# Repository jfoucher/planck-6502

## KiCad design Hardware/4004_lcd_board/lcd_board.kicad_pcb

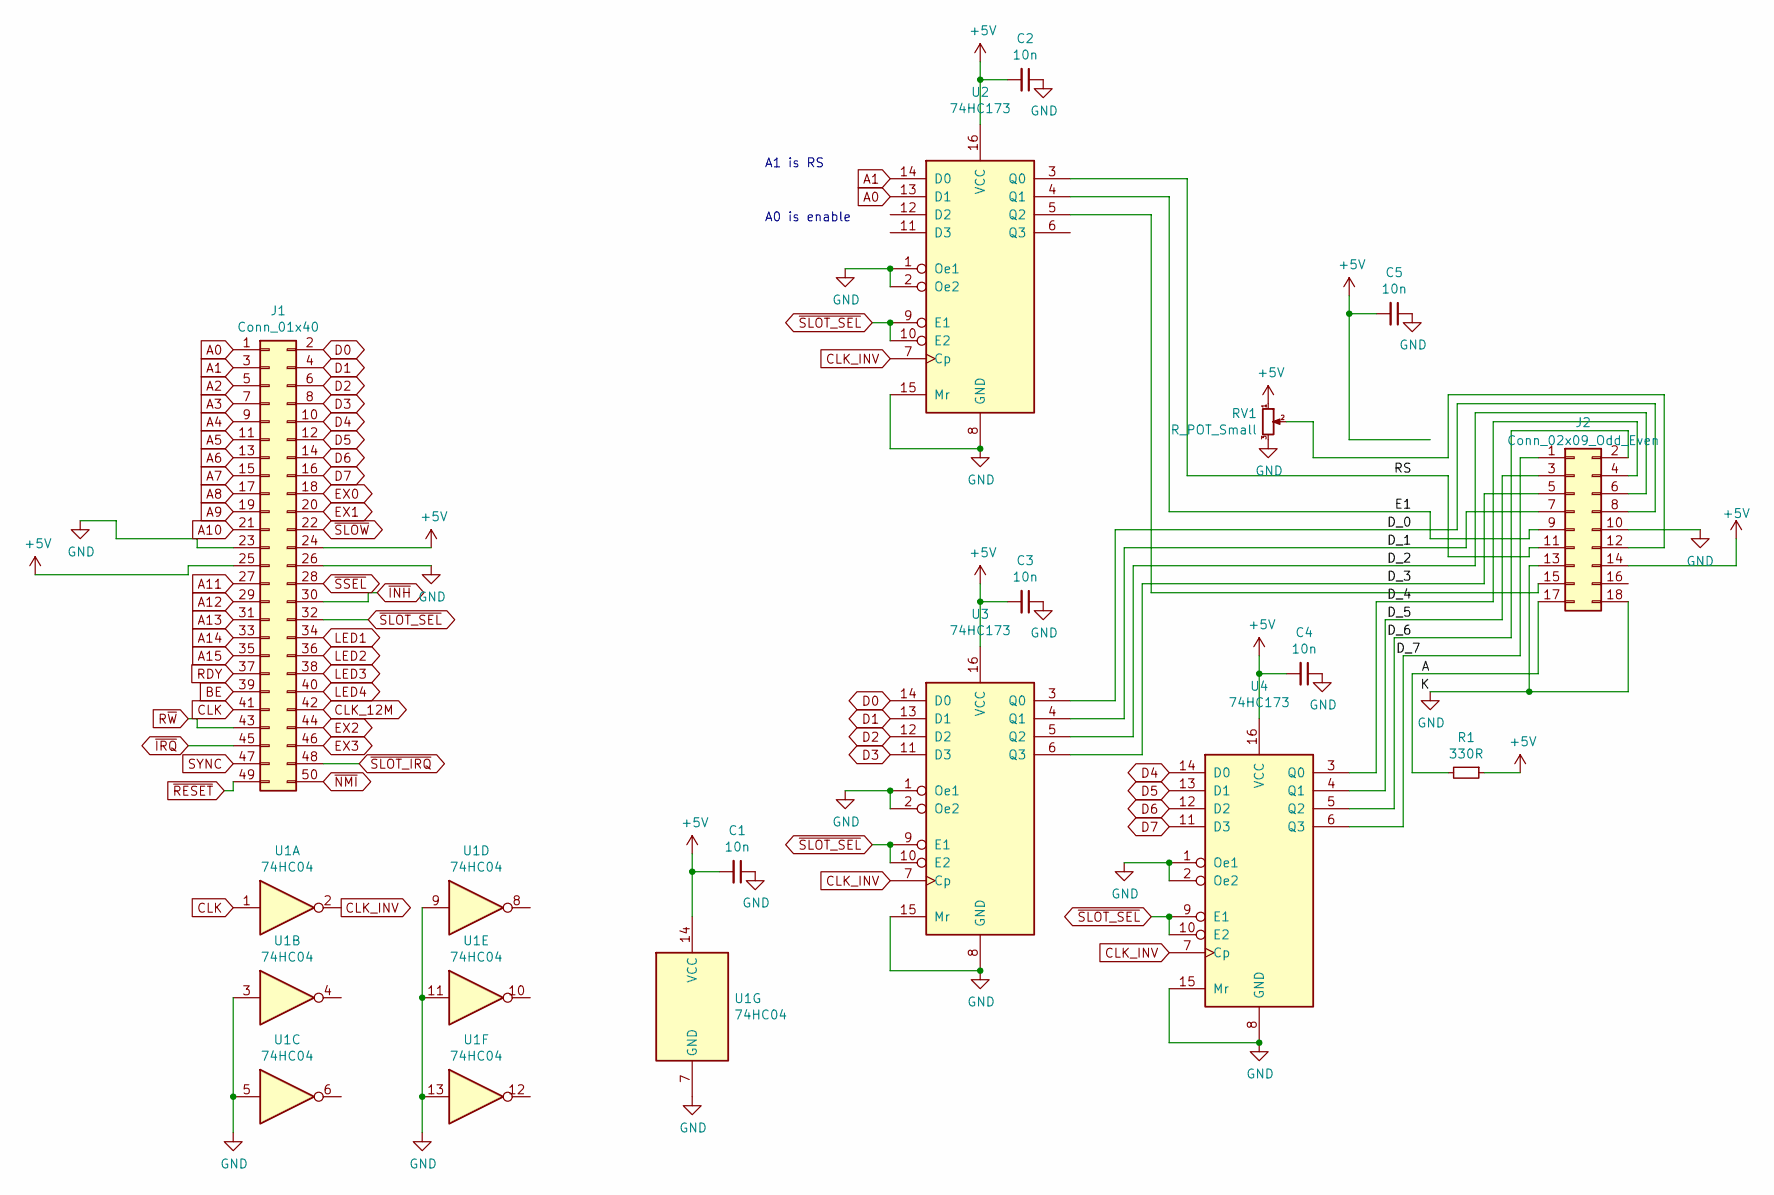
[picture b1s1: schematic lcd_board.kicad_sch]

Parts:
C1, C2, C3, C4, C5: 10n; C_Disc_D4.3mm_W1.9mm_P5.00mm
J1: Conn_01x40; PinHeader_2x25_P2.54mm_Horizontal
J2: Conn_02x09_Odd_Even; PinHeader_2x09_P2.54mm_Horizontal
R1: 330R; R_Axial_DIN0207_L6.3mm_D2.5mm_P10.16mm_Horizontal
RV1: R_POT_Small; Potentiometer_Piher_PT-6-V_Vertical
U1: 74HC04; DIP-14_W7.62mm_Socket
U2, U3, U4: 74HC173; DIP-16_W7.62mm_Socket

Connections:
+5V: C1.2, C2.2, C3.2, C4.2, C5.2, J1.24, J1.25, J2.14, R1.1, RV1.1, U1.14 (VCC), U2.16 (VCC), U3.16 (VCC), U4.16 (VCC)
/A: J2.17, R1.2
/D_0: J2.8, U3.3 (Q0)
/D_1: J2.7, U3.4 (Q1)
/D_2: J2.6, U3.5 (Q2)
/D_3: J2.5, U3.6 (Q3)
/D_4: J2.4, U4.3 (Q0)
/D_5: J2.3, U4.4 (Q1)
/D_6: J2.2, U4.5 (Q2)
/D_7: J2.1, U4.6 (Q3)
/E1: J2.9, U2.4 (Q1)
/RS: J2.11, U2.3 (Q0)
A0: J1.1, U2.13 (D1)
A1: J1.3, U2.14 (D0)
A2: J1.5
A3: J1.7
A4: J1.9
A5: J1.11
A6: J1.13
A7: J1.15
A8: J1.17
A9: J1.19
A10: J1.21
A11: J1.27
A12: J1.29
A13: J1.31
A14: J1.33
A15: J1.35
BE: J1.39
CLK: J1.41, U1.1
CLK_12M: J1.42
CLK_INV: U1.2, U2.7 (Cp), U3.7 (Cp), U4.7 (Cp)
D0: J1.2, U3.14 (D0)
D1: J1.4, U3.13 (D1)
D2: J1.6, U3.12 (D2)
D3: J1.8, U3.11 (D3)
D4: J1.10, U4.14 (D0)
D5: J1.12, U4.13 (D1)
D6: J1.14, U4.12 (D2)
D7: J1.16, U4.11 (D3)
EX0: J1.18
EX1: J1.20
EX2: J1.44
EX3: J1.46
GND: C1.1, C2.1, C3.1, C4.1, C5.1, J1.23, J1.26, J2.10, J2.13, J2.18, RV1.3, U1.3, U1.5, U1.7 (GND), U1.9, U1.11, U1.13, U2.1 (Oe1), U2.2 (Oe2), U2.8 (GND), U2.15 (Mr), U3.1 (Oe1), U3.2 (Oe2), U3.8 (GND), U3.15 (Mr), U4.1 (Oe1), U4.2 (Oe2), U4.8 (GND), U4.15 (Mr)
LED1: J1.34
LED2: J1.36
LED3: J1.38
LED4: J1.40
unnamed: J2.12, RV1.2
unnamed: J2.15, U2.5 (Q2)
RDY: J1.37
R~W: J1.43
SYNC: J1.47
~INH: J1.30
~IRQ: J1.45
~NMI: J1.50
~RESET: J1.49
~SLOT_IRQ: J1.48
~SLOT_SEL: J1.32, U2.9 (E1), U2.10 (E2), U3.9 (E1), U3.10 (E2), U4.9 (E1), U4.10 (E2)
~SLOW: J1.22
~SSEL: J1.28

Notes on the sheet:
A1 is RS
A0 is enable

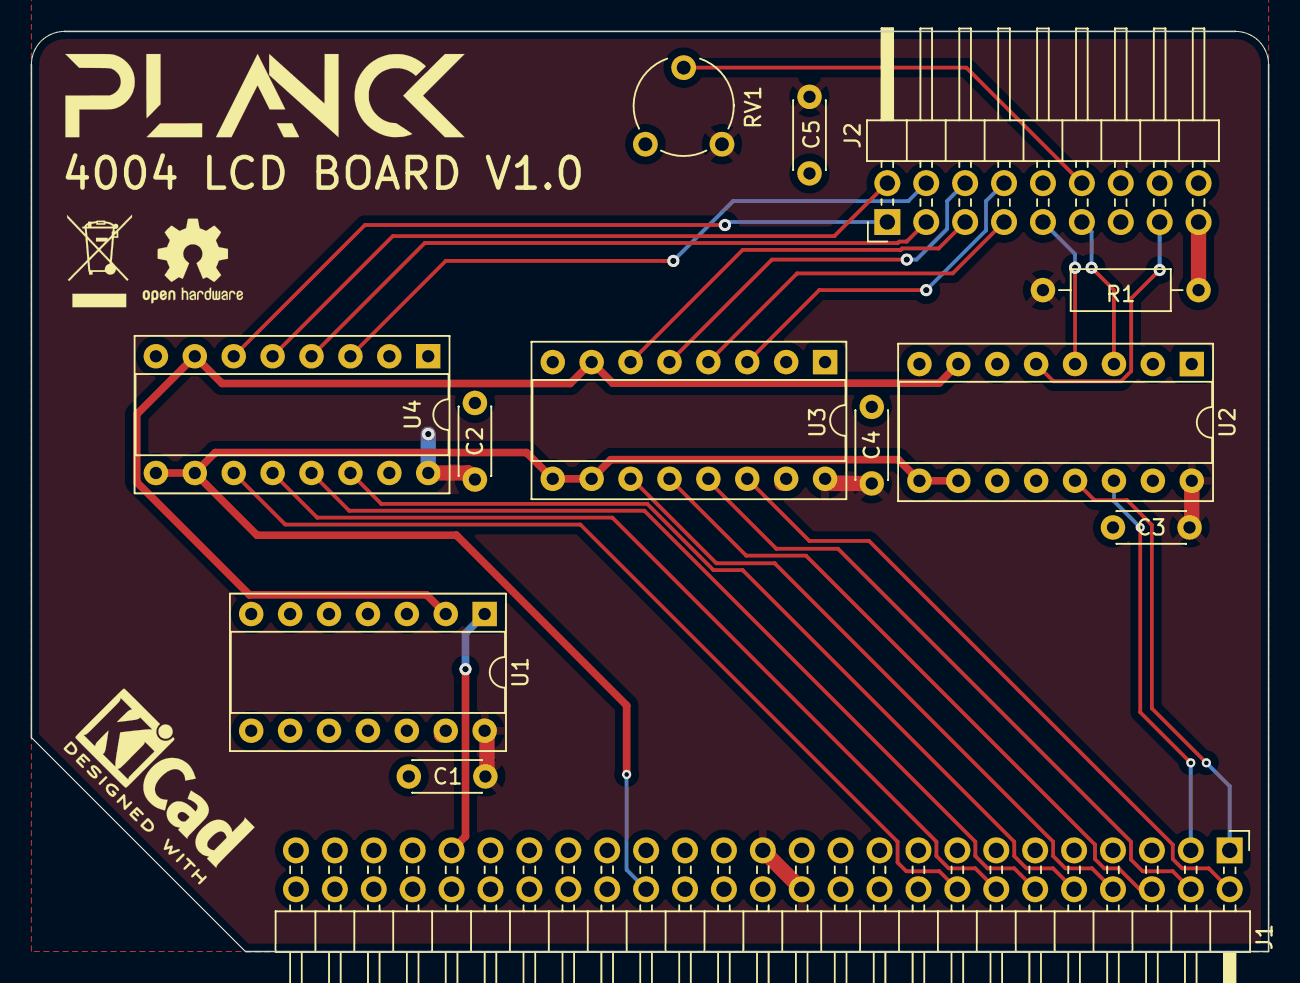
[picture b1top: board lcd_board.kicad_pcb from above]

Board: 2 copper layers, 80.8 x 60.1 mm, 13 parts (0 on the bottom side), 28 nets.

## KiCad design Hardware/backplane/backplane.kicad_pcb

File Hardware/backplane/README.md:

## Planck backplane
This is the backplane of the Planck 6502 computer.
A backplane is a mostly passive board where the daughter boards that actually provide functionality plug in to.

This backplane provides the power input (power is unregulated so you will need to provide a regulated power supply such as a usb adapter). A micro USB socket is provided for this purpose.

### Built in I/O

There is one power switch as well a two push buttons.
The first one triggers the reset pin via a MAX811 reset IC (which also provides power on reset)

The second push button triggers the NMI pin which triggers a "soft reset" of the computer.

In addition to the power LED, there are 4 LEDs that are connected to the expansion bus and can be turned on or off by expansion cards.

### Expansion cards 

There is built in address decoding logic for the expansion slots in the form of a GAL22V10 chip or equivalent. The decoding is very basic and simply sets a signal low that goes to one of the 5 expansion slots. Each expansion card is then responsible for trigerring itself when that signal is low. 

The address range available to each slot can be changed by simply reprogramming the GAL22V10 chip. By default the range `$FF80` to `$FFCF` is reserved for expansion cards. That is 16 bytes of address range for each of the 5 expansion slots

Expansion cards are not forced to honor their select line, it's just the range where they can be sure that the CPU board RAM or ROM will be disconnected from the data bus. We can therefore have a card like a RAM expansion board that can use banking to replace any address range, simply by asserting the INH signal when necessary.
Expansion cards must disconnect from the bus when another slot address range is called, or risk getting bus contention.

### CPU card slot

Slot 0 is special in that it is meant to host the CPU board, which also contains the base RAM and ROM. As such it has no select line, but a signal which indicates if any of the expansion board is selected, so that the rom and ram can be put offline.

A INH signal has also been added. This signal inhibits the built in ROM and RAM on the CPU board and let's the expansion board take over the bus (except for the range reserved for other expansion boards)

### Built-in clock

The onboard oscillator provides the base clock. It is divided by two to provide a stable clock to the peripherals that require it through the `CLK_12M` signal. Cards can assert the SLOW signal to require a slower clock. In that case the clock signal goes through a counter that divides the clock further. This is the `CLK` signal and is the only one that the CPU board listens to.

### Expansion bus signals

Most pins correspond to the pins of the same name on the CPU.

Below are the pins that are specific to the expansion bus:

| Pin | Description |
|-----   |-------------|
| EX0-EX2 | 3 expansion pins that are reserved for future use or can be used for communication betwen two expansion cards.|
| EX3-EX5 | 3 more expansion pins that can be used for card to card communications. These are not connected to lot zero because slot 0 uses these pins to receive IRQs from the expansion cards|
| <span style="text-decoration:overline">INH</span>|When low, this signal inhibits the RAM and ROM present on the CPU card and allows an expansion card to take over the whole bus (except expansion region).|
|<span style="text-decoration:overline">SEL1</span>-<span style="text-decoration:overline">SEL5</span>|The expansion card in the slot in which this signal is low should activate.|
|<span style="text-decoration:overline">SSEL</span>| Slot selected. The cpu card and any other card should disable all bus access when this signal is low and their own select signal (<span style="text-decoration:overline">SEL1</span>-<span style="text-decoration:overline">SEL5</span>) is high.|
|LED1-LED4| Debug leds 1 to 4.|
| <span style="text-decoration:overline">IRQ1</span>-<span style="text-decoration:overline">IRQ5</span>|Should be used by expansion cards when they want to signal an IRQ. All 5 lines are ANDed together on the processor board and pull the <span style="text-decoration:overline">IRQ</span> line low when at least one of them is low.|

### Board view

This is what the board looks like at the moment

<br />This documentation is licensed under a <a rel="license" href="http://creativecommons.org/licenses/by-sa/4.0/">Creative Commons Attribution-ShareAlike 4.0 International License</a>.

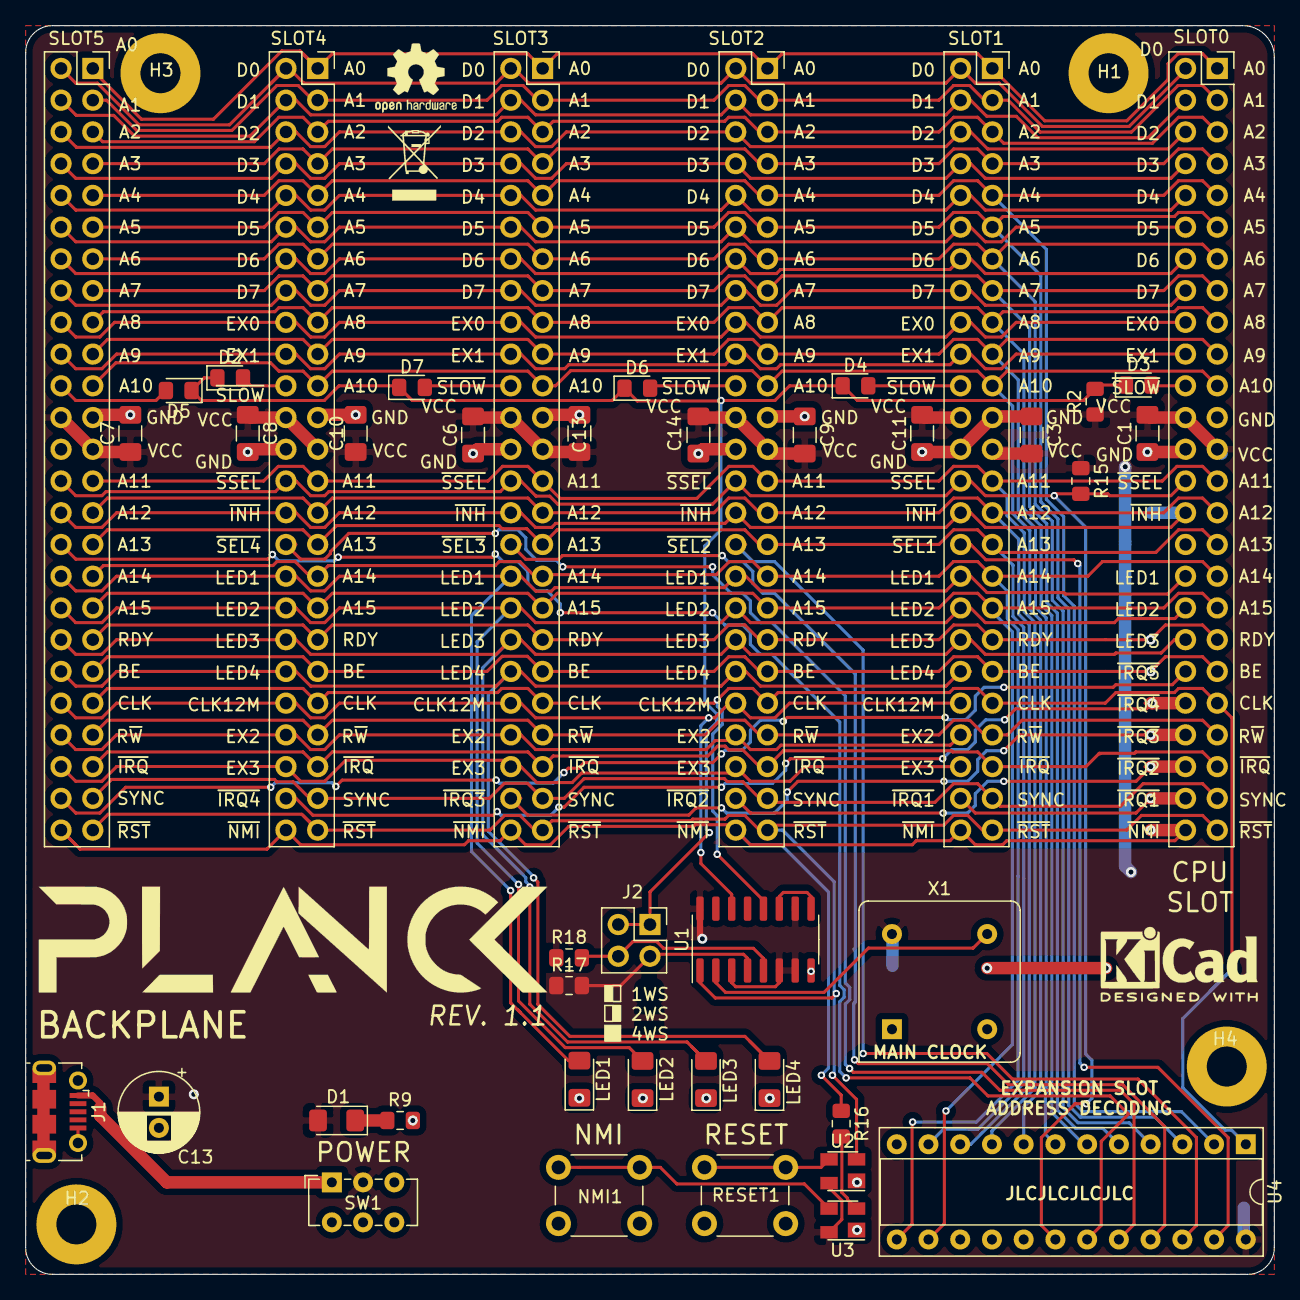
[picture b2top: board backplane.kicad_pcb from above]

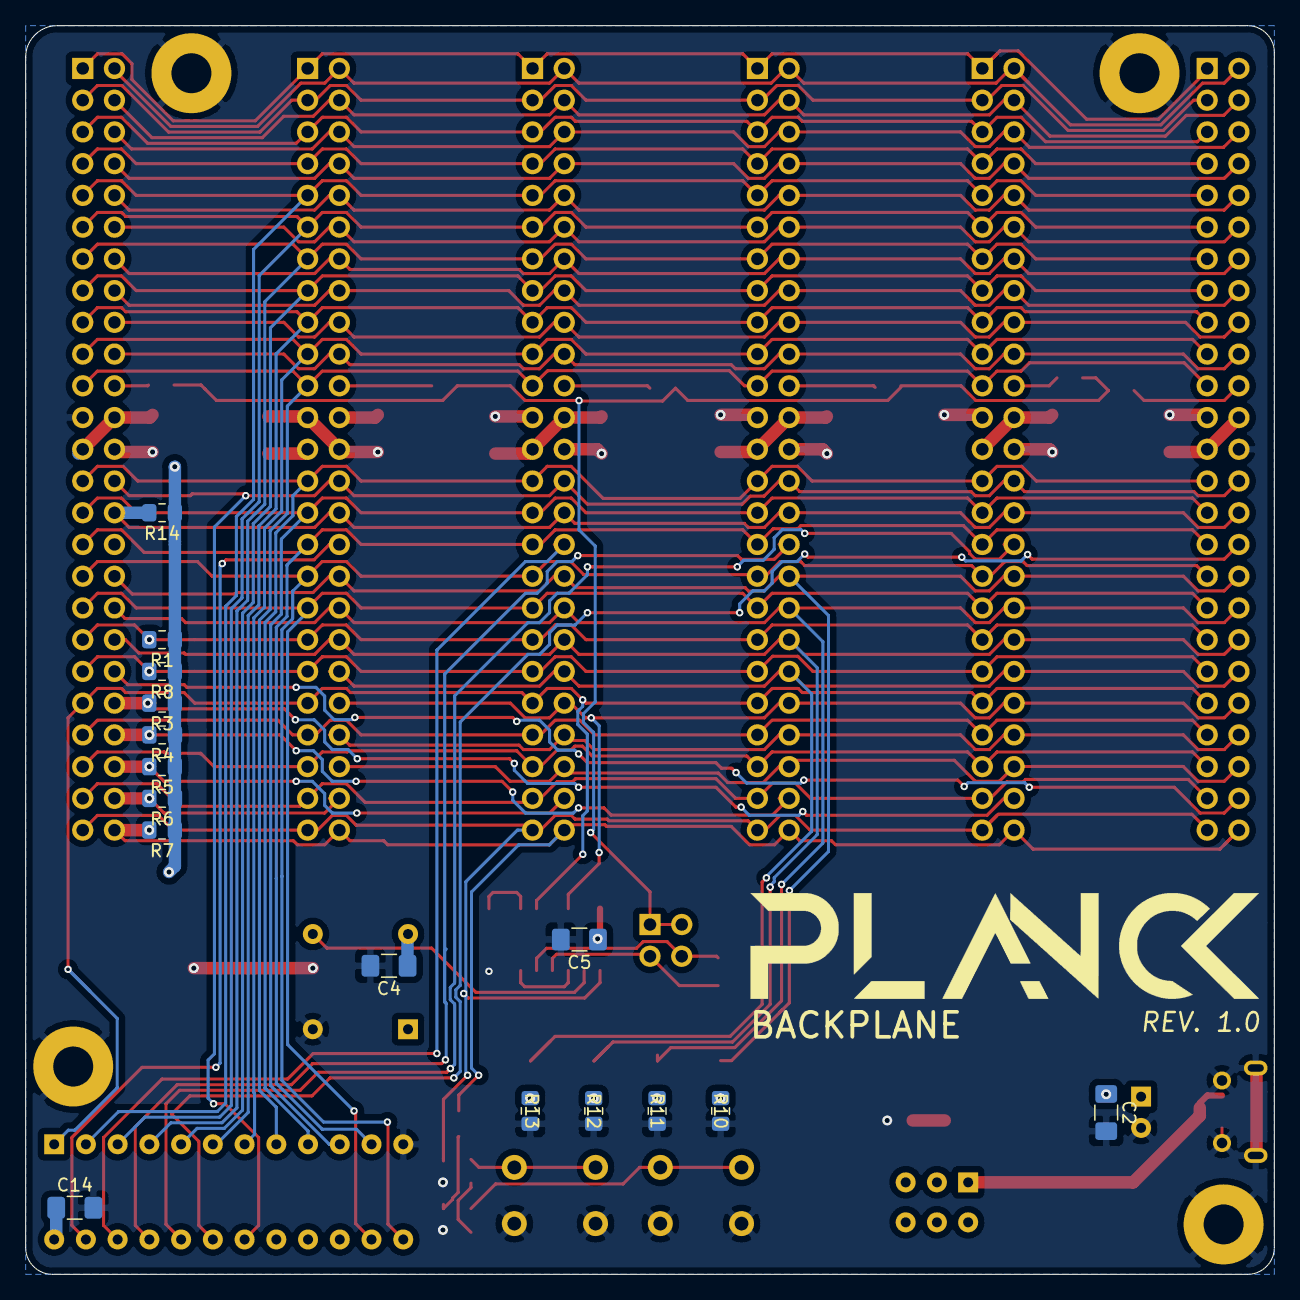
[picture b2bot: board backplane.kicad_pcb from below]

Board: 2 copper layers, 99.9 x 99.9 mm, 64 parts (16 on the bottom side), 75 nets.

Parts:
C1, C2, C3, C4, C5, C6, C7, C8, C9, C10, C11, C13#2, C14, C14#2: C_Small; C_1206_3216Metric_Pad1.42x1.75mm_HandSolder
C13: C_Small; CP_Radial_D6.3mm_P2.50mm
D1: LED; LED_1206_3216Metric_Pad1.42x1.75mm_HandSolder
D2, D3, D4, D5, D6, D7: DIODE; D_0805_2012Metric_Pad1.15x1.40mm_HandSolder
H1, H2, H3, H4: MountingHole_Pad; MountingHole_3.2mm_M3_Pad
J1: USB_B_Micro; USB_Micro-B_Molex-105017-0001
J2: Conn_02x02_Odd_Even; PinHeader_2x02_P2.54mm_Vertical
LED1, LED2, LED3, LED4: LED; LED_1206_3216Metric_Pad1.42x1.75mm_HandSolder
NMI1: SW_Push; SW_PUSH_6mm
R1, R8, R16: 4.7k; R_0805_2012Metric_Pad1.15x1.40mm_HandSolder
R2, R3, R4, R5, R6, R7, R14, R15, R17, R18: 1k; R_0805_2012Metric_Pad1.15x1.40mm_HandSolder
R9, R10, R11, R12, R13: 470R; R_0805_2012Metric_Pad1.15x1.40mm_HandSolder
RESET1: SW_Push; SW_PUSH_6mm
SLOT0, SLOT1, SLOT2, SLOT3, SLOT4, SLOT5: Conn_01x40; PinSocket_2x25_P2.54mm_Vertical
SW1: SW_SPST; SW_E-Switch_EG1271_DPDT
U1: 74AC161; SOIC-16_3.9x9.9mm_P1.27mm
U2, U3: MAX811SEUS-T; SOT-143
U4: PAL24; DIP-24_W7.62mm_Socket
X1: 24MHz; Oscillator_DIP-8

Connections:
+5V: C1.2, C2.1, C3.2, C4.1, C5.1, C6.2, C7.1, C8.1, C9.2, C10.1, C11.2, C13.1, C13#2.2, C14.1, C14#2.1, D1.2, R1.1, R2.1, R3.1, R4.1, R5.1, R6.1, R7.1, R8.1, R14.1, R15.1, R17.1, R18.1, SLOT0.24, SLOT0.25, SLOT1.24, SLOT1.25, SLOT2.24, SLOT2.25, SLOT3.24, SLOT3.25, SLOT4.24, SLOT4.25, SLOT5.24, SLOT5.25, SW1.2, U1.3, U1.6, U1.7, U1.10, U1.16, U2.4, U3.4, U4.24, X1.8
/CLK_24M: U1.2, X1.5
/DS1: J2.2, R17.2, U1.4
/DS2: J2.4, R18.2, U1.5
A0: SLOT0.1, SLOT1.1, SLOT2.1, SLOT3.1, SLOT4.1, SLOT5.1
A1: SLOT0.3, SLOT1.3, SLOT2.3, SLOT3.3, SLOT4.3, SLOT5.3
A2: SLOT0.5, SLOT1.5, SLOT2.5, SLOT3.5, SLOT4.5, SLOT5.5
A3: SLOT0.7, SLOT1.7, SLOT2.7, SLOT3.7, SLOT4.7, SLOT5.7
A4: SLOT0.9, SLOT1.9, SLOT2.9, SLOT3.9, SLOT4.9, SLOT5.9, U4.2
A5: SLOT0.11, SLOT1.11, SLOT2.11, SLOT3.11, SLOT4.11, SLOT5.11, U4.3
A6: SLOT0.13, SLOT1.13, SLOT2.13, SLOT3.13, SLOT4.13, SLOT5.13, U4.4
A7: SLOT0.15, SLOT1.15, SLOT2.15, SLOT3.15, SLOT4.15, SLOT5.15, U4.5
A8: SLOT0.17, SLOT1.17, SLOT2.17, SLOT3.17, SLOT4.17, SLOT5.17, U4.6
A9: SLOT0.19, SLOT1.19, SLOT2.19, SLOT3.19, SLOT4.19, SLOT5.19, U4.7
A10: SLOT0.21, SLOT1.21, SLOT2.21, SLOT3.21, SLOT4.21, SLOT5.21, U4.8
A11: SLOT0.27, SLOT1.27, SLOT2.27, SLOT3.27, SLOT4.27, SLOT5.27, U4.9
A12: SLOT0.29, SLOT1.29, SLOT2.29, SLOT3.29, SLOT4.29, SLOT5.29, U4.10
A13: SLOT0.31, SLOT1.31, SLOT2.31, SLOT3.31, SLOT4.31, SLOT5.31, U4.11
A14: SLOT0.33, SLOT1.33, SLOT2.33, SLOT3.33, SLOT4.33, SLOT5.33, U4.13
A15: SLOT0.35, SLOT1.35, SLOT2.35, SLOT3.35, SLOT4.35, SLOT5.35, U4.14
BE: R8.2, SLOT0.39, SLOT1.39, SLOT2.39, SLOT3.39, SLOT4.39, SLOT5.39
CLK: SLOT0.41, SLOT1.41, SLOT2.41, SLOT3.41, SLOT4.41, SLOT5.41, U1.12, U4.1
CLK_12M: SLOT1.42, SLOT2.42, SLOT3.42, SLOT4.42, SLOT5.42, U1.14
D0: SLOT0.2, SLOT1.2, SLOT2.2, SLOT3.2, SLOT4.2, SLOT5.2
D1: SLOT0.4, SLOT1.4, SLOT2.4, SLOT3.4, SLOT4.4, SLOT5.4
D2: SLOT0.6, SLOT1.6, SLOT2.6, SLOT3.6, SLOT4.6, SLOT5.6
D3: SLOT0.8, SLOT1.8, SLOT2.8, SLOT3.8, SLOT4.8, SLOT5.8
D4: SLOT0.10, SLOT1.10, SLOT2.10, SLOT3.10, SLOT4.10, SLOT5.10
D5: SLOT0.12, SLOT1.12, SLOT2.12, SLOT3.12, SLOT4.12, SLOT5.12
D6: SLOT0.14, SLOT1.14, SLOT2.14, SLOT3.14, SLOT4.14, SLOT5.14
D7: SLOT0.16, SLOT1.16, SLOT2.16, SLOT3.16, SLOT4.16, SLOT5.16
EX0: SLOT0.18, SLOT1.18, SLOT2.18, SLOT3.18, SLOT4.18, SLOT5.18
EX1: SLOT0.20, SLOT1.20, SLOT2.20, SLOT3.20, SLOT4.20, SLOT5.20
EX2: SLOT1.44, SLOT2.44, SLOT3.44, SLOT4.44, SLOT5.44
EX3: SLOT1.46, SLOT2.46, SLOT3.46, SLOT4.46, SLOT5.46
GND: C1.1, C2.2, C3.1, C4.2, C5.2, C6.1, C7.2, C8.2, C9.1, C10.2, C11.1, C13.2, C13#2.1, C14.2, C14#2.2, H1.1, H2.1, H3.1, H4.1, J1.5, J1.6, NMI1.1, R9.2, R10.2, R11.2, R12.2, R13.2, RESET1.1, SLOT0.23, SLOT0.26, SLOT1.23, SLOT1.26, SLOT2.23, SLOT2.26, SLOT3.23, SLOT3.26, SLOT4.23, SLOT4.26, SLOT5.23, SLOT5.26, U1.8, U2.1, U3.1, U4.12, X1.4
LED1: LED1.2, SLOT0.34, SLOT1.34, SLOT2.34, SLOT3.34, SLOT4.34, SLOT5.34
LED2: LED2.2, SLOT0.36, SLOT1.36, SLOT2.36, SLOT3.36, SLOT4.36, SLOT5.36
LED3: LED3.2, SLOT0.38, SLOT1.38, SLOT2.38, SLOT3.38, SLOT4.38, SLOT5.38
LED4: LED4.2, SLOT1.40, SLOT2.40, SLOT3.40, SLOT4.40, SLOT5.40
unnamed: D1.1, R9.1
unnamed: D2.2, SLOT4.22
unnamed: D3.2, SLOT0.22
unnamed: D4.2, SLOT1.22
unnamed: D5.2, SLOT5.22
unnamed: D6.2, SLOT2.22
unnamed: D7.2, SLOT3.22
unnamed: J1.1, SW1.1
unnamed: LED1.1, R10.1
unnamed: LED2.1, R11.1
unnamed: LED3.1, R12.1
unnamed: LED4.1, R13.1
unnamed: NMI1.2, U3.3
unnamed: R16.2, U3.2
unnamed: RESET1.2, U2.3
unnamed: U1.9, U1.11
RDY: R1.2, SLOT0.37, SLOT1.37, SLOT2.37, SLOT3.37, SLOT4.37, SLOT5.37
R~W~: SLOT0.43, SLOT1.43, SLOT2.43, SLOT3.43, SLOT4.43, SLOT5.43
SYNC: SLOT0.47, SLOT1.47, SLOT2.47, SLOT3.47, SLOT4.47, SLOT5.47
~INH~: R14.2, SLOT0.30, SLOT1.30, SLOT2.30, SLOT3.30, SLOT4.30, SLOT5.30
~IRQ1~: R6.2, SLOT0.48, SLOT1.48
~IRQ2~: R5.2, SLOT0.46, SLOT2.48
~IRQ3~: R4.2, SLOT0.44, SLOT3.48
~IRQ4~: R3.2, SLOT0.42, SLOT4.48
~IRQ5~: SLOT0.40, SLOT5.48
~IRQ~: SLOT0.45, SLOT1.45, SLOT2.45, SLOT3.45, SLOT4.45, SLOT5.45
~NMI~: R7.2, R16.1, SLOT0.50, SLOT1.50, SLOT2.50, SLOT3.50, SLOT4.50, SLOT5.50
~RESET~: SLOT0.49, SLOT1.49, SLOT2.49, SLOT3.49, SLOT4.49, SLOT5.49, U1.1, U2.2
~SLOT1~: SLOT1.32, U4.23
~SLOT2~: SLOT2.32, U4.22
~SLOT3~: SLOT3.32, U4.21
~SLOT4~: SLOT4.32, U4.20
~SLOT5~: SLOT5.32, U4.19
~SLOW~: D2.1, D3.1, D4.1, D5.1, D6.1, D7.1, J2.1, J2.3, R2.2
~SSEL~: R15.2, SLOT0.28, SLOT1.28, SLOT2.28, SLOT3.28, SLOT4.28, SLOT5.28, U4.18

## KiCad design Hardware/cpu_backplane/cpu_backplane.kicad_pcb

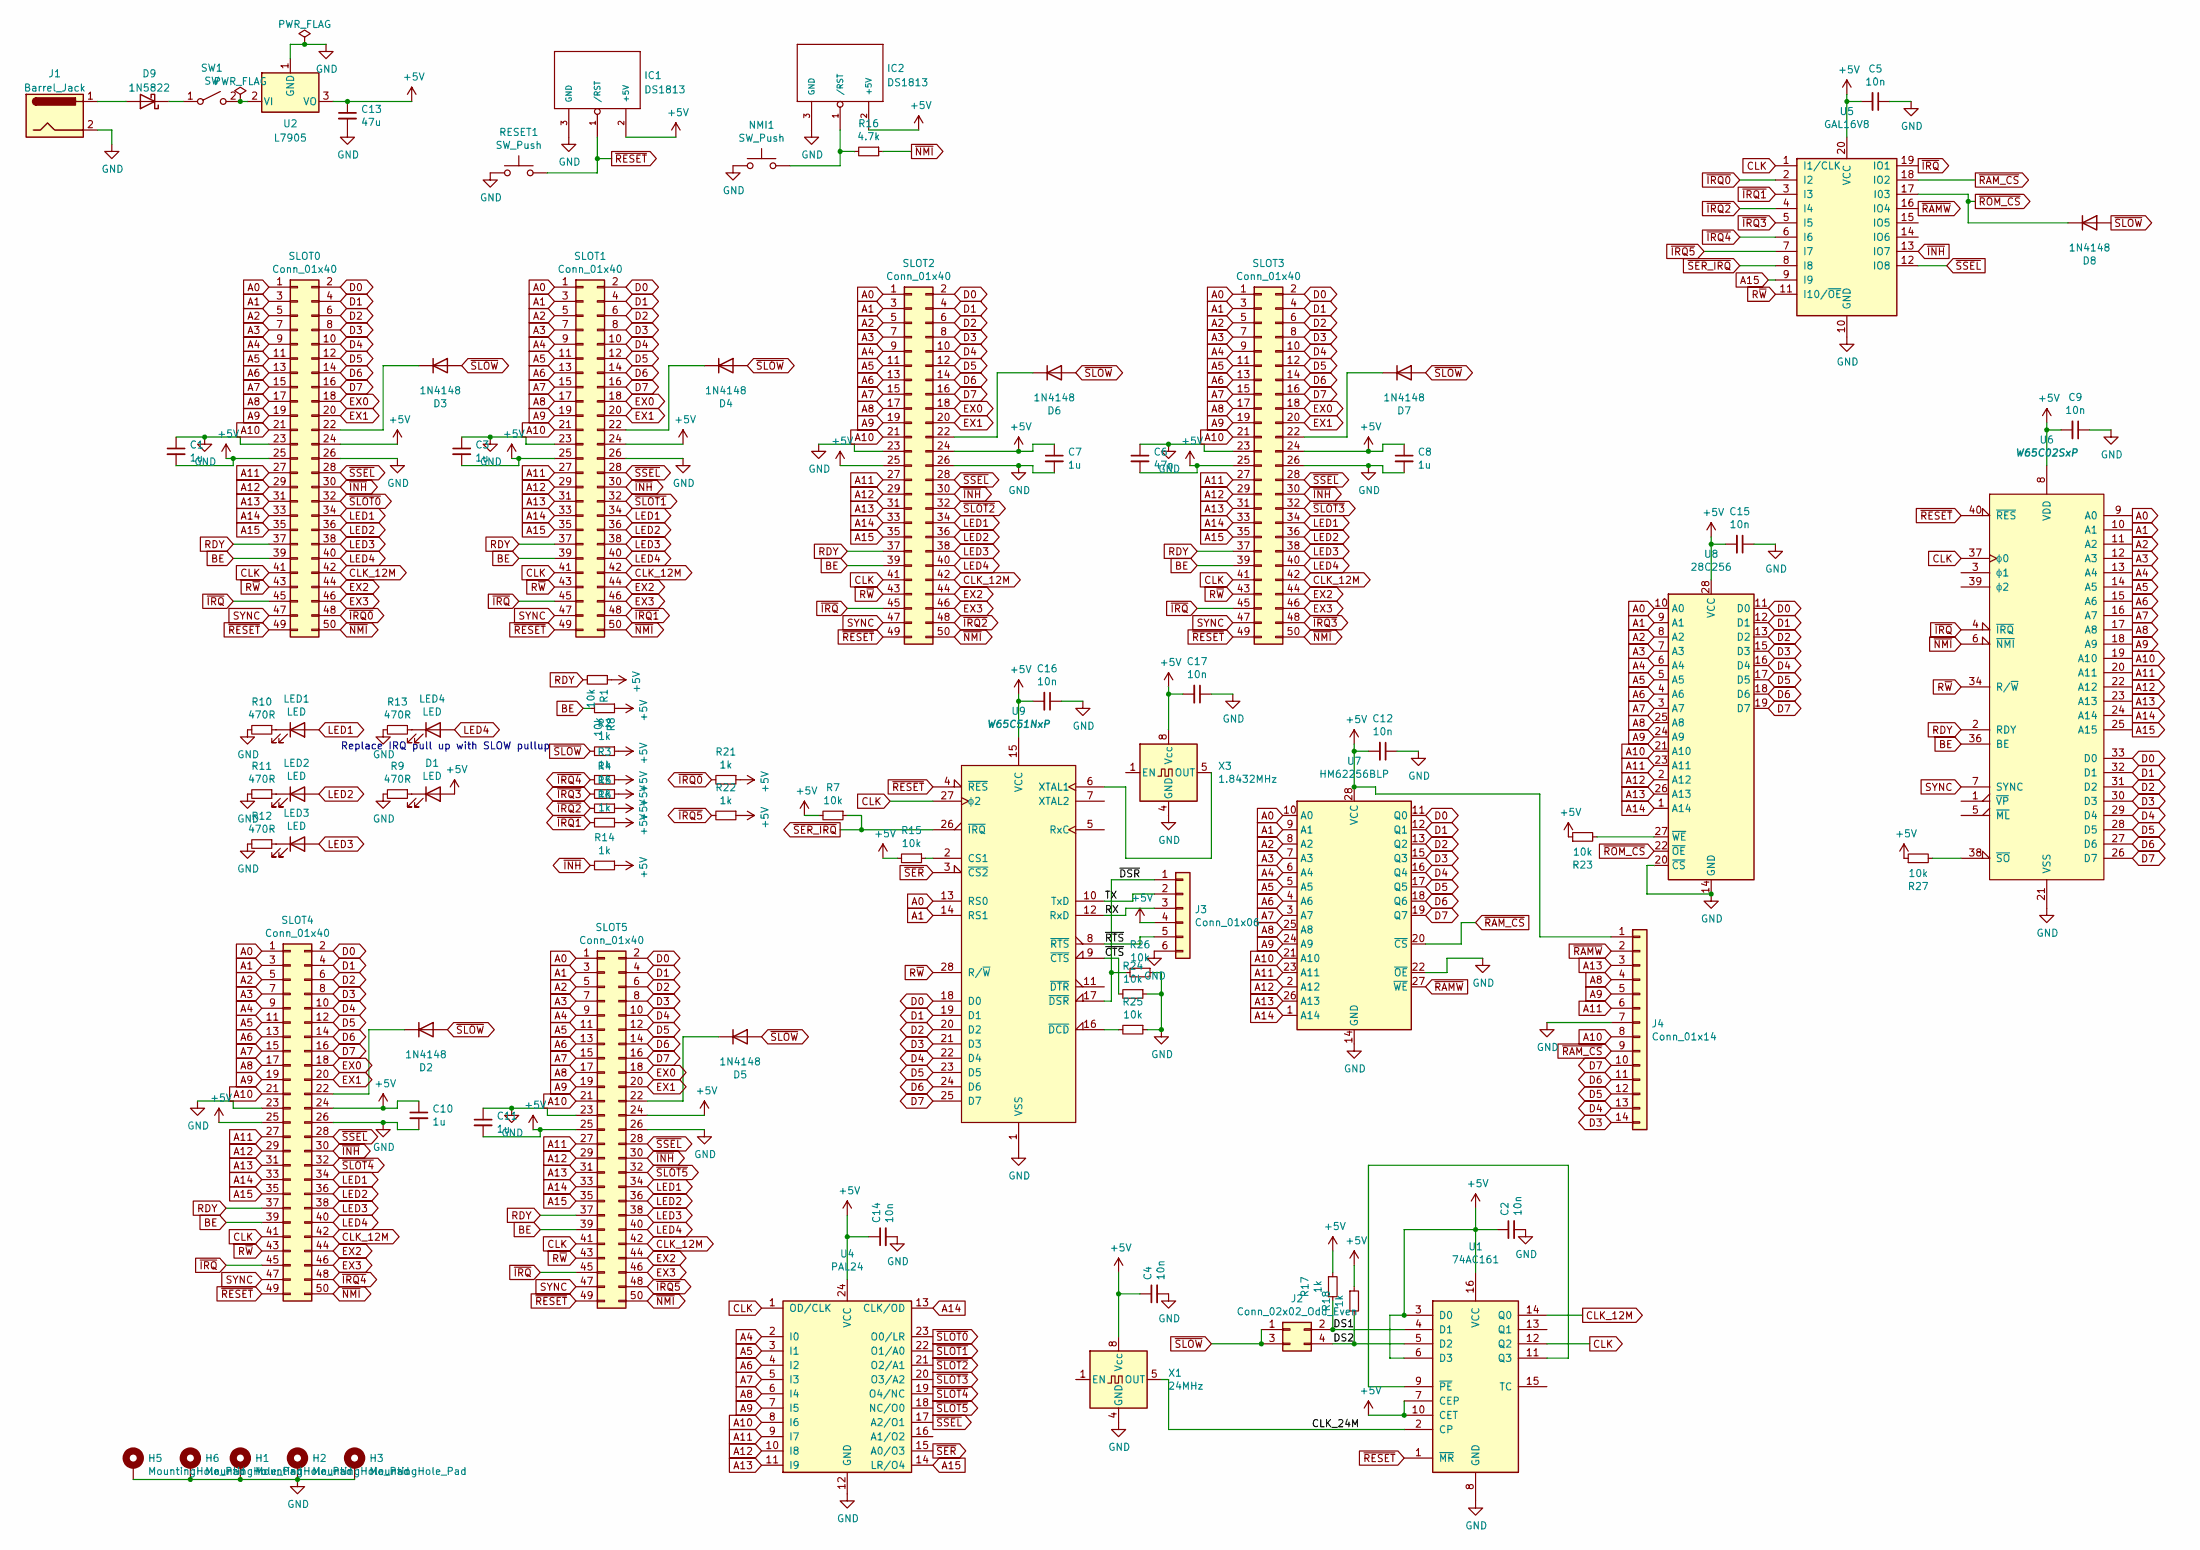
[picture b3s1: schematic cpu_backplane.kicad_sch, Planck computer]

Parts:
C1, C3, C7, C8, C10, C11: 1u; C_Disc_D4.3mm_W1.9mm_P5.00mm
C2, C4, C5, C9, C12, C14, C15, C16, C17: 10n; C_Disc_D4.3mm_W1.9mm_P5.00mm
C6: 47n; C_Disc_D4.3mm_W1.9mm_P5.00mm
C13: 47u; CP_Radial_D6.3mm_P2.50mm
D1: LED; LED_D3.0mm
D2, D3, D4, D5, D6, D7, D8: 1N4148; D_DO-35_SOD27_P7.62mm_Horizontal
D9: 1N5822; D_DO-201AD_P15.24mm_Horizontal
H1, H2, H3, H5, H6: MountingHole_Pad; MountingHole_3.2mm_M3_Pad
IC1: DS1813; TO-92L_Inline
IC2: DS1813; TO-92_Inline
J1: Barrel_Jack; BarrelJack_Horizontal
J2: Conn_02x02_Odd_Even; PinHeader_2x02_P2.54mm_Vertical
J3: Conn_01x06; PinSocket_1x06_P2.54mm_Vertical
J4: Conn_01x14; PinSocket_1x14_P2.54mm_Vertical
LED1, LED2, LED3, LED4: LED; LED_D3.0mm
NMI1: SW_Push; SW_PUSH_6mm
R1, R7, R8, R15, R23, R24, R25, R26: 10k; R_Axial_DIN0207_L6.3mm_D2.5mm_P7.62mm_Horizontal
R2, R3, R4, R5, R6, R14, R17, R18, R21, R22: 1k; R_Axial_DIN0207_L6.3mm_D2.5mm_P7.62mm_Horizontal
R9, R10, R11, R12, R13: 470R; R_Axial_DIN0207_L6.3mm_D2.5mm_P7.62mm_Horizontal
R16: 4.7k; R_Axial_DIN0207_L6.3mm_D2.5mm_P7.62mm_Horizontal
R27: 10k; R_Axial_DIN0204_L3.6mm_D1.6mm_P5.08mm_Horizontal
RESET1: SW_Push; SW_PUSH_6mm
SLOT0, SLOT1, SLOT2, SLOT3, SLOT4, SLOT5: Conn_01x40; PinSocket_2x25_P2.54mm_Vertical
SW1: SW; SW_E-Switch_EG1271_SPDT
U1: 74AC161; DIP-16_W7.62mm_Socket
U2: L7905; TO-220-3_Vertical
U4: PAL24; DIP-24_W7.62mm_Socket
U5: GAL16V8; DIP-20_W7.62mm_Socket
U6: W65C02SxP; DIP-40_W15.24mm_Socket
U7: HM62256BLP; DIP-28_W7.62mm_Socket
U8: 28C256; DIP-28_W15.24mm_Socket
U9: W65C51NxP; DIP-28_W15.24mm_Socket
X1: 24MHz; Oscillator_DIP-8
X3: 1.8432MHz; Oscillator_DIP-8

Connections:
+5V: C1.2, C2.1, C3.2, C4.1, C5.2, C6.2, C7.1, C8.1, C9.2, C10.1, C11.2, C12.2, C13.1, C14.1, C15.2, C16.2, C17.2, D1.2 (A), IC1.2 (+5V), IC2.2 (+5V), J3.4, J4.1, R1.1, R2.1, R3.1, R4.1, R5.1, R6.1, R7.2, R8.1, R14.1, R15.2, R17.1, R18.1, R21.1, R22.1, R23.1, R27.1, SLOT0.24, SLOT0.25, SLOT1.24, SLOT1.25, SLOT2.24, SLOT2.25, SLOT3.24, SLOT3.25, SLOT4.24, SLOT4.25, SLOT5.24, SLOT5.25, U1.3 (D0), U1.6 (D3), U1.7 (CEP), U1.10 (CET), U1.16 (VCC), U2.3 (VO), U4.24 (VCC), U5.20 (VCC), U6.8 (VDD), U7.28 (VCC), U8.28 (VCC), U9.15 (VCC), X1.8 (Vcc), X3.8 (Vcc)
/CLK_24M: U1.2 (CP), X1.5 (OUT)
/DS1: J2.2, R17.2, U1.4 (D1)
/DS2: J2.4, R18.2, U1.5 (D2)
/RX: J3.3, U9.12 (RxD)
/TX: J3.2, U9.10 (TxD)
/~CTS: R24.2, U9.9 (~CTS)
/~DSR: J3.1, R26.2, U9.17 (~DSR)
/~RTS: J3.5, U9.8 (~RTS)
A0: SLOT0.1, SLOT1.1, SLOT2.1, SLOT3.1, SLOT4.1, SLOT5.1, U6.9 (A0), U7.10 (A0), U8.10 (A0), U9.13 (RS0)
A1: SLOT0.3, SLOT1.3, SLOT2.3, SLOT3.3, SLOT4.3, SLOT5.3, U6.10 (A1), U7.9 (A1), U8.9 (A1), U9.14 (RS1)
A2: SLOT0.5, SLOT1.5, SLOT2.5, SLOT3.5, SLOT4.5, SLOT5.5, U6.11 (A2), U7.8 (A2), U8.8 (A2)
A3: SLOT0.7, SLOT1.7, SLOT2.7, SLOT3.7, SLOT4.7, SLOT5.7, U6.12 (A3), U7.7 (A3), U8.7 (A3)
A4: SLOT0.9, SLOT1.9, SLOT2.9, SLOT3.9, SLOT4.9, SLOT5.9, U4.2 (I0), U6.13 (A4), U7.6 (A4), U8.6 (A4)
A5: SLOT0.11, SLOT1.11, SLOT2.11, SLOT3.11, SLOT4.11, SLOT5.11, U4.3 (I1), U6.14 (A5), U7.5 (A5), U8.5 (A5)
A6: SLOT0.13, SLOT1.13, SLOT2.13, SLOT3.13, SLOT4.13, SLOT5.13, U4.4 (I2), U6.15 (A6), U7.4 (A6), U8.4 (A6)
A7: SLOT0.15, SLOT1.15, SLOT2.15, SLOT3.15, SLOT4.15, SLOT5.15, U4.5 (I3), U6.16 (A7), U7.3 (A7), U8.3 (A7)
A8: J4.4, SLOT0.17, SLOT1.17, SLOT2.17, SLOT3.17, SLOT4.17, SLOT5.17, U4.6 (I4), U6.17 (A8), U7.25 (A8), U8.25 (A8)
A9: J4.5, SLOT0.19, SLOT1.19, SLOT2.19, SLOT3.19, SLOT4.19, SLOT5.19, U4.7 (I5), U6.18 (A9), U7.24 (A9), U8.24 (A9)
A10: J4.8, SLOT0.21, SLOT1.21, SLOT2.21, SLOT3.21, SLOT4.21, SLOT5.21, U4.8 (I6), U6.19 (A10), U7.21 (A10), U8.21 (A10)
A11: J4.6, SLOT0.27, SLOT1.27, SLOT2.27, SLOT3.27, SLOT4.27, SLOT5.27, U4.9 (I7), U6.20 (A11), U7.23 (A11), U8.23 (A11)
A12: SLOT0.29, SLOT1.29, SLOT2.29, SLOT3.29, SLOT4.29, SLOT5.29, U4.10 (I8), U6.22 (A12), U7.2 (A12), U8.2 (A12)
A13: J4.3, SLOT0.31, SLOT1.31, SLOT2.31, SLOT3.31, SLOT4.31, SLOT5.31, U4.11 (I9), U6.23 (A13), U7.26 (A13), U8.26 (A13)
A14: SLOT0.33, SLOT1.33, SLOT2.33, SLOT3.33, SLOT4.33, SLOT5.33, U4.13 (CLK/OD), U6.24 (A14), U7.1 (A14), U8.1 (A14)
A15: SLOT0.35, SLOT1.35, SLOT2.35, SLOT3.35, SLOT4.35, SLOT5.35, U4.14 (LR/O4), U5.9 (I9), U6.25 (A15)
BE: R8.2, SLOT0.39, SLOT1.39, SLOT2.39, SLOT3.39, SLOT4.39, SLOT5.39, U6.36 (BE)
CLK: SLOT0.41, SLOT1.41, SLOT2.41, SLOT3.41, SLOT4.41, SLOT5.41, U1.12 (Q2), U4.1 (OD/CLK), U5.1 (I1/CLK), U6.37 (ϕ0), U9.27 (ϕ2)
CLK_12M: SLOT0.42, SLOT1.42, SLOT2.42, SLOT3.42, SLOT4.42, SLOT5.42, U1.14 (Q0)
D0: SLOT0.2, SLOT1.2, SLOT2.2, SLOT3.2, SLOT4.2, SLOT5.2, U6.33 (D0), U7.11 (Q0), U8.11 (D0), U9.18 (D0)
D1: SLOT0.4, SLOT1.4, SLOT2.4, SLOT3.4, SLOT4.4, SLOT5.4, U6.32 (D1), U7.12 (Q1), U8.12 (D1), U9.19 (D1)
D2: SLOT0.6, SLOT1.6, SLOT2.6, SLOT3.6, SLOT4.6, SLOT5.6, U6.31 (D2), U7.13 (Q2), U8.13 (D2), U9.20 (D2)
D3: J4.14, SLOT0.8, SLOT1.8, SLOT2.8, SLOT3.8, SLOT4.8, SLOT5.8, U6.30 (D3), U7.15 (Q3), U8.15 (D3), U9.21 (D3)
D4: J4.13, SLOT0.10, SLOT1.10, SLOT2.10, SLOT3.10, SLOT4.10, SLOT5.10, U6.29 (D4), U7.16 (Q4), U8.16 (D4), U9.22 (D4)
D5: J4.12, SLOT0.12, SLOT1.12, SLOT2.12, SLOT3.12, SLOT4.12, SLOT5.12, U6.28 (D5), U7.17 (Q5), U8.17 (D5), U9.23 (D5)
D6: J4.11, SLOT0.14, SLOT1.14, SLOT2.14, SLOT3.14, SLOT4.14, SLOT5.14, U6.27 (D6), U7.18 (Q6), U8.18 (D6), U9.24 (D6)
D7: J4.10, SLOT0.16, SLOT1.16, SLOT2.16, SLOT3.16, SLOT4.16, SLOT5.16, U6.26 (D7), U7.19 (Q7), U8.19 (D7), U9.25 (D7)
EX0: SLOT0.18, SLOT1.18, SLOT2.18, SLOT3.18, SLOT4.18, SLOT5.18
EX1: SLOT0.20, SLOT1.20, SLOT2.20, SLOT3.20, SLOT4.20, SLOT5.20
EX2: SLOT0.44, SLOT1.44, SLOT2.44, SLOT3.44, SLOT4.44, SLOT5.44
EX3: SLOT0.46, SLOT1.46, SLOT2.46, SLOT3.46, SLOT4.46, SLOT5.46
GND: C1.1, C2.2, C3.1, C4.2, C5.1, C6.1, C7.2, C8.2, C9.1, C10.2, C11.1, C12.1, C13.2, C14.2, C15.1, C16.1, C17.1, H1.1, H2.1, H3.1, H5.1, H6.1, IC1.3 (GND), IC2.3 (GND), J1.2, J3.6, J4.7, NMI1.1, R9.2, R10.2, R11.2, R12.2, R13.2, R24.1, R25.1, R26.1, RESET1.1, SLOT0.23, SLOT0.26, SLOT1.23, SLOT1.26, SLOT2.23, SLOT2.26, SLOT3.23, SLOT3.26, SLOT4.23, SLOT4.26, SLOT5.23, SLOT5.26, U1.8 (GND), U2.1 (GND), U4.12 (GND), U5.10 (GND), U6.21 (VSS), U7.14 (GND), U7.22 (~OE), U8.14 (GND), U8.20 (~CS), U9.1 (VSS), X1.4 (GND), X3.4 (GND)
LED1: LED1.2 (A), SLOT0.34, SLOT1.34, SLOT2.34, SLOT3.34, SLOT4.34, SLOT5.34
LED2: LED2.2 (A), SLOT0.36, SLOT1.36, SLOT2.36, SLOT3.36, SLOT4.36, SLOT5.36
LED3: LED3.2 (A), SLOT0.38, SLOT1.38, SLOT2.38, SLOT3.38, SLOT4.38, SLOT5.38
LED4: LED4.2 (A), SLOT0.40, SLOT1.40, SLOT2.40, SLOT3.40, SLOT4.40, SLOT5.40
unnamed: D1.1 (K), R9.1
unnamed: D2.1 (K), SLOT4.22
unnamed: D3.1 (K), SLOT0.22
unnamed: D4.1 (K), SLOT1.22
unnamed: D5.1 (K), SLOT5.22
unnamed: D6.1 (K), SLOT2.22
unnamed: D7.1 (K), SLOT3.22
unnamed: D9.1 (K), SW1.1 (A)
unnamed: D9.2 (A), J1.1
unnamed: IC2.1 (/RST), NMI1.2, R16.2
unnamed: LED1.1 (K), R10.1
unnamed: LED2.1 (K), R11.1
unnamed: LED3.1 (K), R12.1
unnamed: LED4.1 (K), R13.1
unnamed: R15.1, U9.2 (CS1)
unnamed: R23.2, U8.27 (~WE)
unnamed: R25.2, U9.16 (~DCD)
unnamed: R27.2, U6.38 (~SO)
unnamed: SW1.2 (B), U2.2 (VI)
unnamed: U1.9 (~PE), U1.11 (Q3)
unnamed: U9.6 (XTAL1), X3.5 (OUT)
RDY: R1.2, SLOT0.37, SLOT1.37, SLOT2.37, SLOT3.37, SLOT4.37, SLOT5.37, U6.2 (RDY)
R~W: SLOT0.43, SLOT1.43, SLOT2.43, SLOT3.43, SLOT4.43, SLOT5.43, U5.11 (I10/~OE), U6.34 (R/~W), U9.28 (R/~W)
SYNC: SLOT0.47, SLOT1.47, SLOT2.47, SLOT3.47, SLOT4.47, SLOT5.47, U6.7 (SYNC)
~INH: R14.2, SLOT0.30, SLOT1.30, SLOT2.30, SLOT3.30, SLOT4.30, SLOT5.30, U5.13 (IO7)
~IRQ0: R21.2, SLOT0.48, U5.2 (I2)
~IRQ1: R6.2, SLOT1.48, U5.3 (I3)
~IRQ2: R5.2, SLOT2.48, U5.4 (I4)
~IRQ3: R4.2, SLOT3.48, U5.5 (I5)
~IRQ4: R3.2, SLOT4.48, U5.6 (I6)
~IRQ5: R22.2, SLOT5.48, U5.7 (I7)
~IRQ: SLOT0.45, SLOT1.45, SLOT2.45, SLOT3.45, SLOT4.45, SLOT5.45, U5.19 (IO1), U6.4 (~IRQ)
~NMI: R16.1, SLOT0.50, SLOT1.50, SLOT2.50, SLOT3.50, SLOT4.50, SLOT5.50, U6.6 (~NMI)
~RAMW: J4.2, U5.16 (IO4), U7.27 (~WE)
~RAM_CS: J4.9, U5.18 (IO2), U7.20 (~CS)
~RESET: IC1.1 (/RST), RESET1.2, SLOT0.49, SLOT1.49, SLOT2.49, SLOT3.49, SLOT4.49, SLOT5.49, U1.1 (~MR), U6.40 (~RES), U9.4 (~RES)
~ROM_CS: D8.1 (K), U5.17 (I03), U8.22 (~OE)
~SER_IRQ: R7.1, U5.8 (I8), U9.26 (~IRQ)
~SER: U4.15 (A0/O3), U9.3 (~CS2)
~SLOT0: SLOT0.32, U4.23 (O0/LR)
~SLOT1: SLOT1.32, U4.22 (O1/A0)
~SLOT2: SLOT2.32, U4.21 (O2/A1)
~SLOT3: SLOT3.32, U4.20 (O3/A2)
~SLOT4: SLOT4.32, U4.19 (O4/NC)
~SLOT5: SLOT5.32, U4.18 (NC/O0)
~SLOW: D2.2 (A), D3.2 (A), D4.2 (A), D5.2 (A), D6.2 (A), D7.2 (A), D8.2 (A), J2.1, J2.3, R2.2
~SSEL: SLOT0.28, SLOT1.28, SLOT2.28, SLOT3.28, SLOT4.28, SLOT5.28, U4.17 (A2/O1), U5.12 (IO8)

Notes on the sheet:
Replace IRQ pull up with SLOW pullup

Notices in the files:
Hardware/cpu_backplane/cpu_backplane.kicad_pcb:
©Jonathan Foucher 2021
